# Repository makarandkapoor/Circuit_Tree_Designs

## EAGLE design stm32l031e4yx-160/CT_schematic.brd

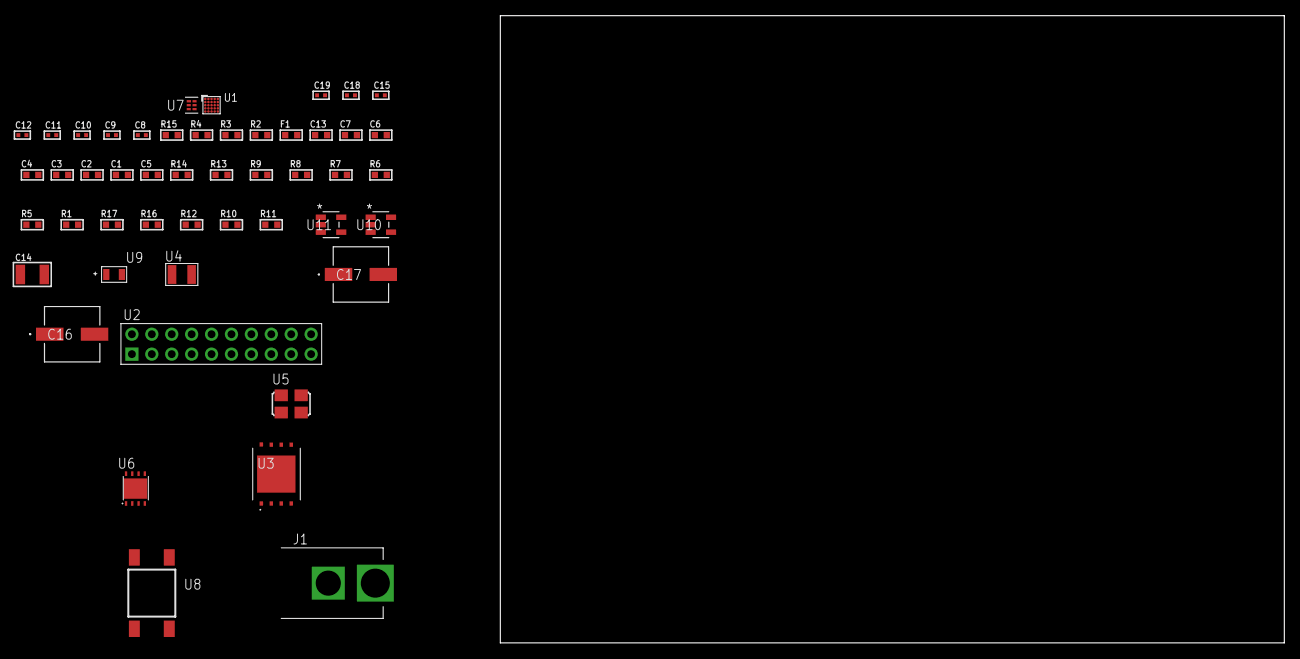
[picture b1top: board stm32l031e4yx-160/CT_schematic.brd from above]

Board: 2 copper layers, 100.0 x 80.0 mm, 49 parts (0 on the bottom side), 25 nets, no tracks yet.

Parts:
C1, C2, C3, C4: 1e-07; C0603
C5: 4.7e-06; C0603
C6: 1e-08; C0603
C7: 1e-06; C0603
C8, C9: 1e-11; C0402
C10, C15: 1e-07; C0402
C11, C12, C18, C19: 1e-08; C0402
C13: 8e-07; R0603
C14: 1e-05; C1210
C16, C17: 0.0001; EXV-9H
F1: 240.0; L0603
J1: PJ-037B; PJ-037B_PACKAGE
R1, R5, R6, R7, R8, R9, R13, R14: 10000.0; R0603
R2: 1000.0; R0603
R3: 1600.5; R0603
R4: 4700.0; R0603
R10, R12: 100000.0; R0603
R11: 153694.38; R0603
R15: 9100.0; R0603
R16: 680000.0; R0603
R17: 120000.0; R0603
U1: STM32L031E4Y6; WLCSP25
U2: TST-110-05-T-D-RA
U3: S25FL128SDPNFI001; WNG008
U4: ABS07-32.768KHZ-7-T
U5: ASFL1-12MHZ-NCS; ASFL1
U6: LP2951ACSDX/NOPB; WSON-8
U7: TPS3895ADRYR; SON-6
U8: 4-1437565-2; SW_4-1437565-2
U9: Q65110A2395; LGM67K-G1J2-24-Z
U10, U11: nc7sz125m5x; NC7SZ125M5X

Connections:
CLK_CRYSTAL_U1_B5: C8.1, U1.B5, U4.1
CLK_CRYSTAL_U1_C5: C9.1, U1.C5, U4.2
GND: C1.2, C2.2, C3.2, C4.2, C5.2, C6.2, C7.2, C8.2, C9.2, C10.2, C11.2, C12.2, C13.2, C14.2, C15.2, C16.2, C17.2, C18.2, C19.2, J1.2, R2.2, R5.2, R12.2, R15.2, R17.2, U1.E1, U2.4, U2.6, U2.8, U2.10, U2.12, U2.14, U2.16, U2.18, U2.20, U3.4, U3.PAD, U5.2, U6.3, U6.4, U6.PAD, U7.2, U9.C, U10.2, U10.3, U11.1, U11.3
NET_U1_A5: R5.1, U1.A5
NET_U1_C4: C6.1, C7.1, F1.1, U1.C4
NET_U1_D5: R4.1, U1.D5, U11.4
NET_U1_E4: R3.1, U1.E4, U9.A
NET_U1_E5: R1.1, U1.E5, U5.3, U8.3, U8.4
NET_U3_3: R7.1, U3.3
NET_U3_7: R9.1, U3.7
NET_U6_5: R10.1, U6.5
NET_U6_7: R11.2, R12.1, U6.7
NET_U7_1: R14.1, R15.1, U7.1
NET_U7_3: R16.2, R17.1, U7.3
NET_U7_4: R13.1, U7.4, U10.4, U11.2
NET_U8_1: R2.1, U8.1, U8.2
PROC_SPI1_MISO: U1.E2, U3.2
PROC_SPI1_MOSI: U1.C3, U3.5
PROC_SPI1_NSS: R8.1, U1.B3, U3.1
PROC_SPI1_SCK: U1.B2, U3.6
PROC_SYS_SWCLK: U1.A2, U2.9
PROC_SYS_SWDIO: U1.A1, U2.7
RST_OUT_U2_SRESET_B: R6.1, U2.15, U10.1
VCC_S1_12V7: C13.1, C16.1, C17.1, J1.1, U6.8
VCC_TIER1_3V3: C1.1, C2.1, C3.1, C4.1, C5.1, C10.1, C11.1, C12.1, C14.1, C15.1, C18.1, C19.1, F1.2, R1.2, R3.2, R4.2, R6.2, R7.2, R8.2, R9.2, R10.2, R11.1, R13.2, R14.2, R16.1, U1.D1, U2.1, U3.8, U5.4, U6.1, U7.6, U10.5, U11.5

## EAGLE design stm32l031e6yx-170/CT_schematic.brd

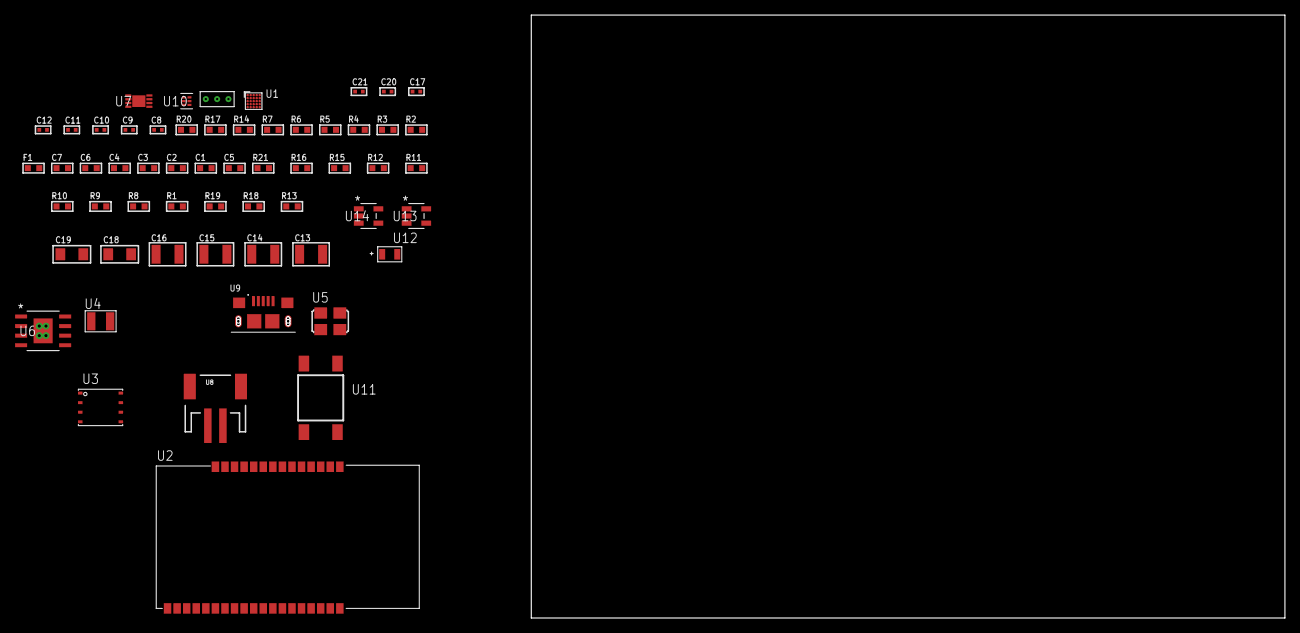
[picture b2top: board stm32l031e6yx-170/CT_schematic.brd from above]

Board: 2 copper layers, 58 parts (0 on the bottom side), 31 nets, no tracks yet.

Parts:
C1, C2, C3, C4: 1e-07; C0603
C5: 4.7e-06; C0603
C6: 1e-08; C0603
C7: 1e-06; C0603
C8, C9: 1e-11; C0402
C10, C17: 1e-07; C0402
C11, C12, C20, C21: 1e-08; C0402
C13, C14, C15, C16: 1e-05; C1210
C18, C19: 1e-05; C1206
F1: 240.0; L0603
R1, R8, R9, R10, R11, R12, R15, R16, R21: 10000.0; R0603
R2: 1000.0; R0603
R3: 1600.5; R0603
R4, R5: 4700.0; R0603
R6, R7, R14: 2200.0; R0603
R13: 4031.5447154472; R0603
R17: 9100.0; R0603
R18: 680000.0; R0603
R19: 120000.0; R0603
R20: 2000.0; R0603
U1: STM32L031E6Y6; WLCSP25
U2: ETRX3587
U3: 24AA512-I/MF; DFN8-S
U4: ABS07-32.768KHZ-7-T
U5: ASFL1-12MHZ-NCS; ASFL1
U6: MIC5234YME; SOIC-8_EP
U7: MCP73831T-2ACI/MC; DFN8_2X3MC
U8: S2B-PH-SM4-TB(LF)(SN); JST-2-SMD
U9: 10118193-0001LF; FCI_10118193-0001LF
U10: TPS3895ADRYR; SON-6
U11: 4-1437565-2; SW_4-1437565-2
U12: Q65110A2395; LGM67K-G1J2-24-Z
U13, U14: nc7sz125m5x; NC7SZ125M5X
U15: Dummy; DUMMY_PACKAGE_122

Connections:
CLK_CRYSTAL_U1_B5: C8.1, U1.B5, U4.1
CLK_CRYSTAL_U1_C5: C9.1, U1.C5, U4.2
GND: C1.2, C2.2, C3.2, C4.2, C5.2, C6.2, C7.2, C8.2, C9.2, C10.2, C11.2, C12.2, C13.2, C14.2, C15.2, C16.2, C17.2, C18.2, C19.2, C20.2, C21.2, R2.2, R8.2, R9.2, R12.2, R14.2, R17.2, R19.2, R20.2, U1.E1, U2.1, U2.13, U2.19, U2.20, U2.31, U2.33, U3.4, U3.7, U5.2, U6.7, U6.EPAD, U7.6, U7.9, U8.2, U9.5, U9.6, U9.7, U9.8, U9.9, U10.2, U12.C, U13.1, U13.3, U14.1, U14.3, U15.1
INPUT_USBPOWER_5V: C18.1, R21.2, U7.1, U7.2, U9.1
NET_U1_A3: R6.1, U1.A3, U3.6
NET_U1_A4: R7.1, U1.A4, U3.5
NET_U1_A5: R8.1, U1.A5
NET_U1_C4: C6.1, C7.1, F1.1, U1.C4
NET_U1_D5: R5.1, U1.D5, U14.4
NET_U1_E4: R3.1, U1.E4, U12.A
NET_U1_E5: R1.1, U1.E5, U5.3, U11.3, U11.4
NET_U2_7: R4.1, U2.7, U13.4
NET_U2_21: R9.1, U2.21
NET_U3_1: R10.1, U3.1
NET_U3_2: R11.1, U3.2
NET_U3_3: R12.1, U3.3
NET_U6_4: R13.2, R14.1, U6.4
NET_U7_5: R21.1, U7.5
NET_U7_8: R20.1, U7.8
NET_U10_1: R16.1, R17.1, U10.1
NET_U10_3: R18.2, R19.1, U10.3
NET_U10_4: R15.1, U10.4, U13.2, U14.2
NET_U11_1: R2.1, U11.1, U11.2
PROC_LPUART1_CTS: U1.E3, U2.8
PROC_LPUART1_RTS: U1.D2, U2.6
PROC_LPUART1_RX: U1.A1, U2.17
PROC_LPUART1_TX: U1.A2, U2.18
PROC_TIM2_CH2: U1.B2, U15.3
PROC_TIM2_CH3: U1.D4, U15.2
VCC_S1_3V7: C13.1, C14.1, C19.1, U6.5, U6.8, U7.3, U7.4, U8.1
VCC_TIER1_3V3: C1.1, C2.1, C3.1, C4.1, C5.1, C10.1, C11.1, C12.1, C15.1, C16.1, C17.1, C20.1, C21.1, F1.2, R1.2, R3.2, R4.2, R5.2, R6.2, R7.2, R10.2, R11.2, R13.1, R15.2, R16.2, R18.1, U1.D1, U2.32, U3.8, U5.4, U6.1, U10.6, U13.5, U14.5

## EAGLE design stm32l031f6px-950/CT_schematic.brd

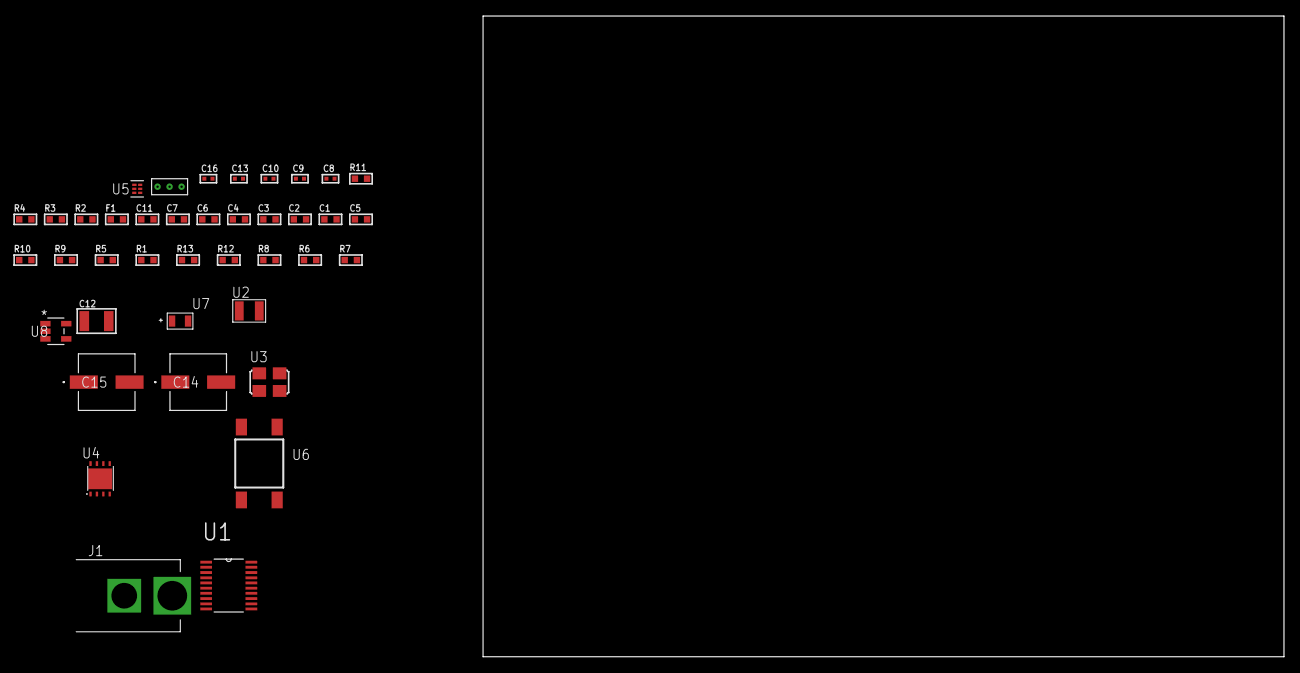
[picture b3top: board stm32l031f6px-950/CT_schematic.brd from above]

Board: 2 copper layers, 100.0 x 80.0 mm, 40 parts (0 on the bottom side), 19 nets, no tracks yet.

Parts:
C1, C2, C3, C4: 1e-07; C0603
C5: 4.7e-06; C0603
C6: 1e-08; C0603
C7, C11: 1e-06; C0603
C8, C9: 1e-11; C0402
C10, C16: 1e-08; C0402
C12: 1e-05; C1210
C13: 1e-07; C0402
C14, C15: 0.0001; EXV-9H
F1: 240.0; L0603
J1: PJ-037B; PJ-037B_PACKAGE
R1, R5, R9, R10: 10000.0; R0603
R2: 1000.0; R0603
R3: 1600.5; R0603
R4: 4700.0; R0603
R6, R8: 100000.0; R0603
R7: 153694.38; R0603
R11: 9100.0; R0603
R12: 680000.0; R0603
R13: 120000.0; R0603
U1: STM32L031F6P6; TSSOP20
U2: ABS07-32.768KHZ-7-T
U3: ASFL1-12MHZ-NCS; ASFL1
U4: LP2951ACSDX/NOPB; WSON-8
U5: TPS3895ADRYR; SON-6
U6: 4-1437565-2; SW_4-1437565-2
U7: Q65110A2395; LGM67K-G1J2-24-Z
U8: nc7sz125m5x; NC7SZ125M5X
U9: Dummy; DUMMY_PACKAGE_78

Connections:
CLK_CRYSTAL_U1_2: C8.1, U1.2, U2.1
CLK_CRYSTAL_U1_3: C9.1, U1.3, U2.2
CLK_U1_6: U1.6, U3.3
GND: C1.2, C2.2, C3.2, C4.2, C5.2, C6.2, C7.2, C8.2, C9.2, C10.2, C11.2, C12.2, C13.2, C14.2, C15.2, C16.2, J1.2, R2.2, R5.2, R8.2, R11.2, R13.2, U1.15, U3.2, U4.3, U4.4, U4.PAD, U5.2, U7.C, U8.1, U8.3, U9.1
NET_U1_1: R5.1, U1.1
NET_U1_4: R4.1, U1.4, U8.4
NET_U1_5: C6.1, C7.1, F1.1, U1.5
NET_U1_19: R3.1, U1.19, U7.A
NET_U1_20: R1.1, U1.20, U6.3, U6.4
NET_U4_5: R6.1, U4.5
NET_U4_7: R7.2, R8.1, U4.7
NET_U5_1: R10.1, R11.1, U5.1
NET_U5_3: R12.2, R13.1, U5.3
NET_U5_4: R9.1, U5.4, U8.2
NET_U6_1: R2.1, U6.1, U6.2
PROC_ADC_IN4: U1.10, U9.2
PROC_ADC_IN6: U1.12, U9.3
VCC_S1_10V3: C11.1, C14.1, C15.1, J1.1, U4.8
VCC_TIER1_3V3: C1.1, C2.1, C3.1, C4.1, C5.1, C10.1, C12.1, C13.1, C16.1, F1.2, R1.2, R3.2, R4.2, R6.2, R7.1, R9.2, R10.2, R12.1, U1.16, U3.4, U4.1, U5.6, U8.5

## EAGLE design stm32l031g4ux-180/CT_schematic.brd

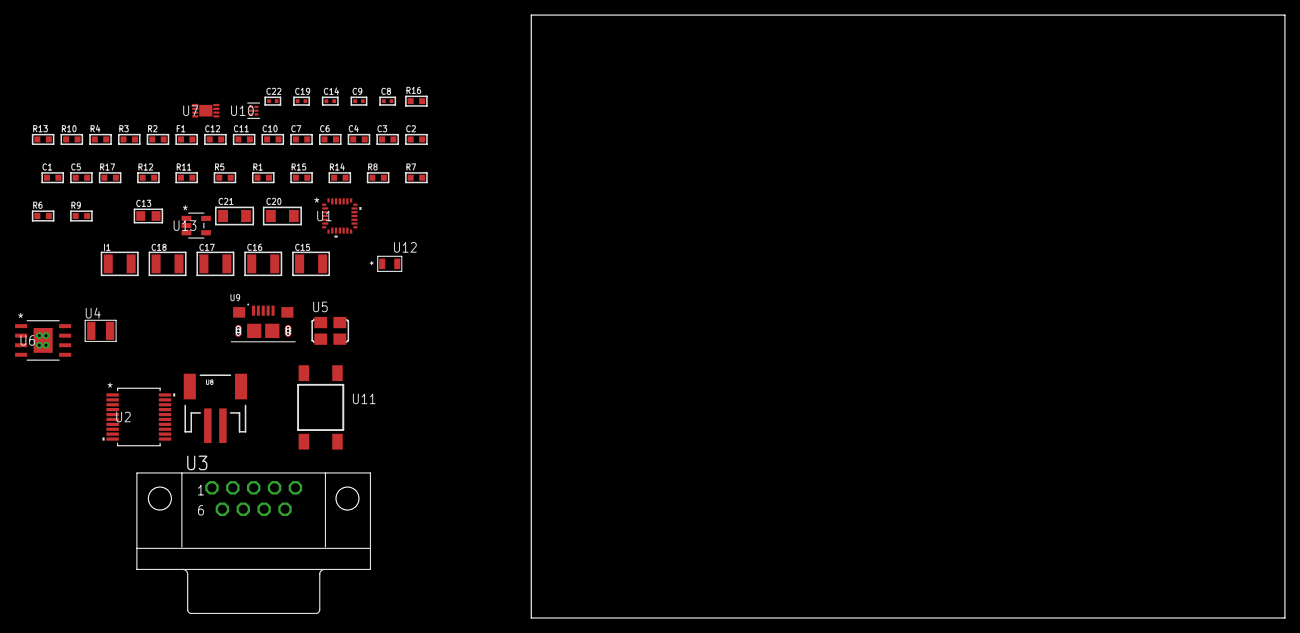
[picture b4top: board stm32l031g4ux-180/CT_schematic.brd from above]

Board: 2 copper layers, 54 parts (0 on the bottom side), 35 nets, no tracks yet.

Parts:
C1, C2, C3, C4: 1e-07; C0603
C5: 4.7e-06; C0603
C6: 1e-08; C0603
C7, C10, C11, C12: 1e-06; C0603
C8, C9: 1e-11; C0402
C13: 4.7e-06; C0805
C14, C22: 1e-08; C0402
C15, C16, C17, C18: 1e-05; C1210
C19: 1e-07; C0402
C20, C21: 1e-05; C1206
F1: 240.0; L0603
I1: 1.5e-05; L1210
R1, R5, R11, R12, R17: 10000.0; R0603
R2: 1000.0; R0603
R3: 1600.5; R0603
R4: 4700.0; R0603
R6, R7, R8: 100000.0; R0603
R9: 4031.5447154472; R0603
R10: 2200.0; R0603
R13: 9100.0; R0603
R14: 680000.0; R0603
R15: 120000.0; R0603
R16: 2000.0; R0603
U1: STM32L031G4U6; UFQFPN28
U2: MAX3218EAP+T; SSOP-20
U3: 182-009-113R531; 182-009-MALE
U4: ABS07-32.768KHZ-7-T
U5: ASFL1-12MHZ-NCS; ASFL1
U6: MIC5234YME; SOIC-8_EP
U7: MCP73831T-2ACI/MC; DFN8_2X3MC
U8: S2B-PH-SM4-TB(LF)(SN); JST-2-SMD
U9: 10118193-0001LF; FCI_10118193-0001LF
U10: TPS3895ADRYR; SON-6
U11: 4-1437565-2; SW_4-1437565-2
U12: Q65110A2395; LGM67K-G1J2-24-Z
U13: nc7sz125m5x; NC7SZ125M5X

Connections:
CLK_CRYSTAL_U1_2: C8.1, U1.2, U4.1
CLK_CRYSTAL_U1_3: C9.1, U1.3, U4.2
CLK_U1_6: U1.6, U5.3
GND: C1.2, C2.2, C3.2, C4.2, C5.2, C6.2, C7.2, C8.2, C9.2, C10.2, C11.2, C12.2, C14.2, C15.2, C16.2, C17.2, C18.2, C19.2, C20.2, C21.2, C22.2, R2.2, R5.2, R10.2, R13.2, R15.2, R16.2, U1.16, U1.28, U2.5, U2.17, U2.20, U3.5, U5.2, U6.7, U6.EPAD, U7.6, U7.9, U8.2, U9.5, U9.6, U9.7, U9.8, U9.9, U10.2, U12.C, U13.1, U13.3
INPUT_USBPOWER_5V: C20.1, R17.2, U7.1, U7.2, U9.1
NET_U1_4: R4.1, U1.4, U13.4
NET_U1_5: C6.1, C7.1, F1.1, U1.5
NET_U1_25: R3.1, U1.25, U12.A
NET_U1_26: R1.1, U1.26, U11.3, U11.4
NET_U1_27: R5.1, U1.27
NET_U2_1: I1.1, U2.1
NET_U2_2: R6.1, U2.2
NET_U2_3: R7.1, U2.3
NET_U2_4: R8.1, U2.4
NET_U2_15: C12.1, U2.15
NET_U2_16: C13.2, U2.16
NET_U2_18: C13.1, U2.18
NET_U2_19: C11.1, U2.19
NET_U3_2: U2.12, U3.2
NET_U3_3: U2.14, U3.3
NET_U3_7: U2.11, U3.7
NET_U3_8: U2.13, U3.8
NET_U6_4: R9.2, R10.1, U6.4
NET_U7_5: R17.1, U7.5
NET_U7_8: R16.1, U7.8
NET_U10_1: R12.1, R13.1, U10.1
NET_U10_3: R14.2, R15.1, U10.3
NET_U10_4: R11.1, U10.4, U13.2
NET_U11_1: R2.1, U11.1, U11.2
PROC_LPUART1_CTS: U1.12, U2.8
PROC_LPUART1_RTS: U1.15, U2.10
PROC_LPUART1_RX: U1.9, U2.9
PROC_LPUART1_TX: U1.8, U2.7
VCC_S1_3V7: C15.1, C16.1, C21.1, U6.5, U6.8, U7.3, U7.4, U8.1
VCC_TIER1_3V3: C1.1, C2.1, C3.1, C4.1, C5.1, C10.1, C14.1, C17.1, C18.1, C19.1, C22.1, F1.2, I1.2, R1.2, R3.2, R4.2, R6.2, R7.2, R8.2, R9.1, R11.2, R12.2, R14.1, U1.1, U1.17, U2.6, U5.4, U6.1, U10.6, U13.5

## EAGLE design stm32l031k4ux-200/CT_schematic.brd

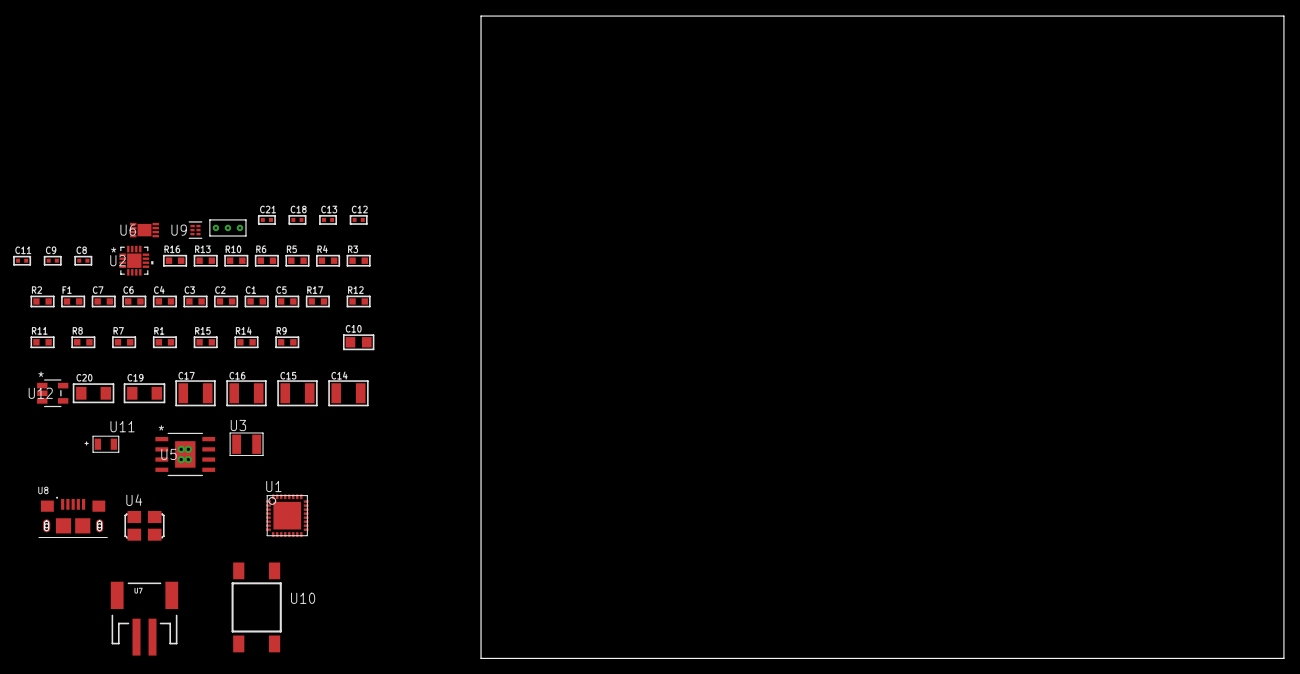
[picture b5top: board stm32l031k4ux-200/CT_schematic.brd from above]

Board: 2 copper layers, 154.3 x 80.0 mm, 52 parts (0 on the bottom side), 25 nets, no tracks yet.

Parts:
C1, C2, C3, C4: 1e-07; C0603
C5: 4.7e-06; C0603
C6: 1e-08; C0603
C7: 1e-06; C0603
C8, C9: 1e-11; C0402
C10: 4.7e-06; C0805
C11, C12, C18: 1e-07; C0402
C13, C21: 1e-08; C0402
C14, C15, C16, C17: 1e-05; C1210
C19, C20: 1e-05; C1206
F1: 240.0; L0603
R1, R7, R8, R11, R12, R17: 10000.0; R0603
R2: 1000.0; R0603
R3: 1600.5; R0603
R4: 4700.0; R0603
R5, R6, R10: 2200.0; R0603
R9: 4031.5447154472; R0603
R13: 9100.0; R0603
R14: 680000.0; R0603
R15: 120000.0; R0603
R16: 2000.0; R0603
U1: STM32L031K4U6; UFQFPN32
U2: MMA8451QT; QFN-16
U3: ABS07-32.768KHZ-7-T
U4: ASFL1-12MHZ-NCS; ASFL1
U5: MIC5234YME; SOIC-8_EP
U6: MCP73831T-2ACI/MC; DFN8_2X3MC
U7: S2B-PH-SM4-TB(LF)(SN); JST-2-SMD
U8: 10118193-0001LF; FCI_10118193-0001LF
U9: TPS3895ADRYR; SON-6
U10: 4-1437565-2; SW_4-1437565-2
U11: Q65110A2395; LGM67K-G1J2-24-Z
U12: nc7sz125m5x; NC7SZ125M5X
U13: Dummy; DUMMY_PACKAGE_107

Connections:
CLK_CRYSTAL_U1_2: C8.1, U1.2, U3.1
CLK_CRYSTAL_U1_3: C9.1, U1.3, U3.2
CLK_U1_6: U1.6, U4.3
GND: C1.2, C2.2, C3.2, C4.2, C5.2, C6.2, C7.2, C8.2, C9.2, C10.2, C11.2, C12.2, C13.2, C14.2, C15.2, C16.2, C17.2, C18.2, C19.2, C20.2, C21.2, R2.2, R7.2, R8.2, R10.2, R13.2, R15.2, R16.2, U1.EPAD, U2.5, U2.10, U2.12, U2.17, U4.2, U5.7, U5.EPAD, U6.6, U6.9, U7.2, U8.5, U8.6, U8.7, U8.8, U8.9, U9.2, U11.C, U12.1, U12.3, U13.1
INPUT_USBPOWER_5V: C19.1, R17.2, U6.1, U6.2, U8.1
NET_U1_4: R4.1, U1.4, U12.4
NET_U1_5: C6.1, C7.1, F1.1, U1.5
NET_U1_19: R5.1, U1.19, U2.4
NET_U1_20: R6.1, U1.20, U2.6
NET_U1_30: R3.1, U1.30, U11.A
NET_U1_31: R7.1, U1.31
NET_U1_32: R1.1, U1.32, U10.3, U10.4
NET_U2_2: C12.1, U2.2
NET_U2_7: R8.1, U2.7
NET_U5_4: R9.2, R10.1, U5.4
NET_U6_5: R17.1, U6.5
NET_U6_8: R16.1, U6.8
NET_U9_1: R12.1, R13.1, U9.1
NET_U9_3: R14.2, R15.1, U9.3
NET_U9_4: R11.1, U9.4, U12.2
NET_U10_1: R2.1, U10.1, U10.2
PROC_TIM2_CH3: U1.8, U13.3
PROC_TIM2_CH4: U1.9, U13.2
VCC_S1_3V7: C14.1, C15.1, C20.1, U5.5, U5.8, U6.3, U6.4, U7.1
VCC_TIER1_3V3: C1.1, C2.1, C3.1, C4.1, C5.1, C10.1, C11.1, C13.1, C16.1, C17.1, C18.1, C21.1, F1.2, R1.2, R3.2, R4.2, R5.2, R6.2, R9.1, R11.2, R12.2, R14.1, U1.1, U1.17, U2.1, U2.14, U4.4, U5.1, U9.6, U12.5

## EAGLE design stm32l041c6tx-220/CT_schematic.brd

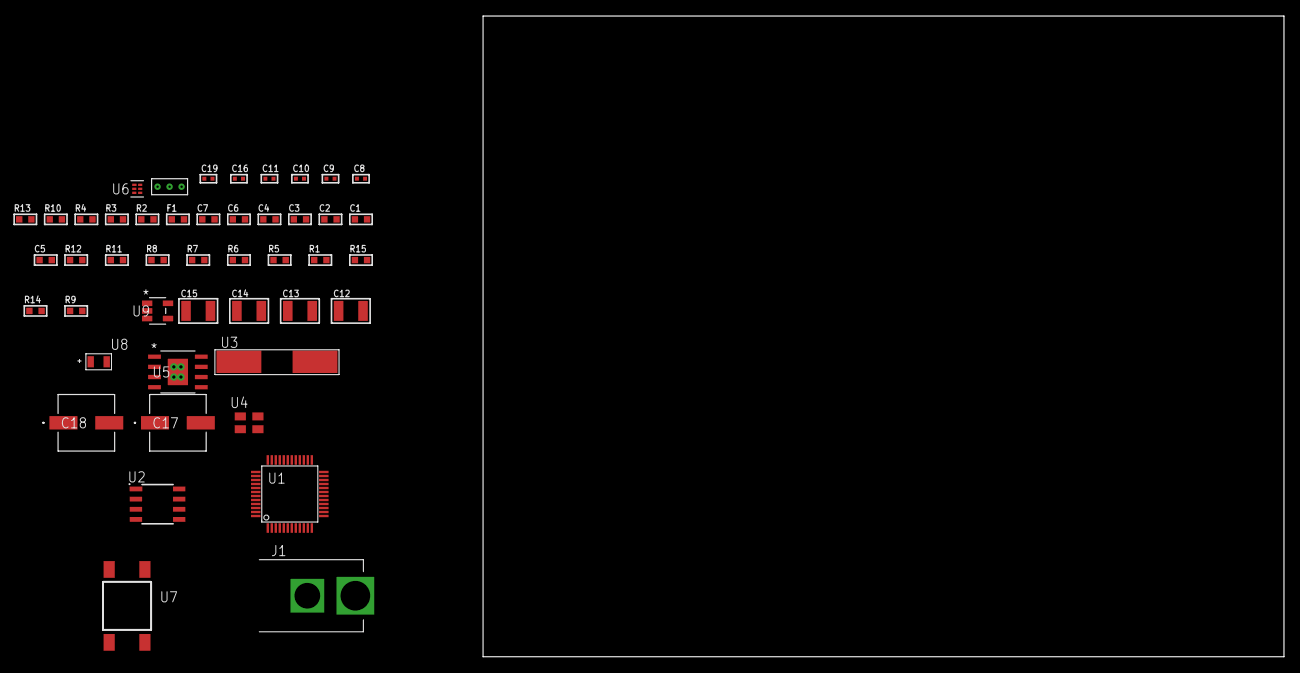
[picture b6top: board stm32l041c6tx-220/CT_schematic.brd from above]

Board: 2 copper layers, 100.0 x 80.0 mm, 46 parts (0 on the bottom side), 24 nets, no tracks yet.

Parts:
C1, C2, C3, C4: 1e-07; C0603
C5: 4.7e-06; C0603
C6: 1e-08; C0603
C7: 1e-06; C0603
C8, C9: 1e-11; C0402
C10, C11, C19: 1e-08; C0402
C12, C13, C14, C15: 1e-05; C1210
C16: 1e-07; C0402
C17, C18: 0.0001; EXV-9H
F1: 240.0; L0603
J1: PJ-037B; PJ-037B_PACKAGE
R1, R5, R6, R7, R8, R11, R12: 10000.0; R0603
R2: 1000.0; R0603
R3: 1600.5; R0603
R4: 4700.0; R0603
R9: 4031.5447154472; R0603
R10: 2200.0; R0603
R13: 9100.0; R0603
R14: 680000.0; R0603
R15: 120000.0; R0603
U1: STM32L041C6T6; LQFP48
U2: AT25M01-SSHM-T; SOIC-8
U3: ABLS-25.000MHZ-B2F-T
U4: ASEK-32.768KHz-ECST; ASEK
U5: MIC5234YME; SOIC-8_EP
U6: TPS3895ADRYR; SON-6
U7: 4-1437565-2; SW_4-1437565-2
U8: Q65110A2395; LGM67K-G1J2-24-Z
U9: nc7sz125m5x; NC7SZ125M5X
U10: Dummy; DUMMY_PACKAGE_90

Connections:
CLK_CRYSTAL_U1_5: C8.1, U1.5, U3.1
CLK_CRYSTAL_U1_6: C9.1, U1.6, U3.2
CLK_U1_3: U1.3, U4.3
GND: C1.2, C2.2, C3.2, C4.2, C5.2, C6.2, C7.2, C8.2, C9.2, C10.2, C11.2, C12.2, C13.2, C14.2, C15.2, C16.2, C17.2, C18.2, C19.2, J1.2, R2.2, R5.2, R10.2, R13.2, R15.2, U1.8, U1.23, U1.35, U1.47, U2.4, U4.2, U5.7, U5.EPAD, U6.2, U8.C, U9.1, U9.3, U10.1
NET_U1_7: R4.1, U1.7, U9.4
NET_U1_9: C6.1, C7.1, F1.1, U1.9
NET_U1_44: R5.1, U1.44
NET_U1_45: R3.1, U1.45, U8.A
NET_U1_46: R1.1, U1.46, U7.3, U7.4
NET_U2_3: R6.1, U2.3
NET_U2_7: R8.1, U2.7
NET_U5_4: R9.2, R10.1, U5.4
NET_U6_1: R12.1, R13.1, U6.1
NET_U6_3: R14.2, R15.1, U6.3
NET_U6_4: R11.1, U6.4, U9.2
NET_U7_1: R2.1, U7.1, U7.2
PROC_ADC_IN1: U1.11, U10.3
PROC_ADC_IN9: U1.19, U10.2
PROC_SPI1_MISO: U1.16, U2.2
PROC_SPI1_MOSI: U1.17, U2.5
PROC_SPI1_NSS: R7.1, U1.14, U2.1
PROC_SPI1_SCK: U1.15, U2.6
VCC_S1_14V3: C12.1, C13.1, C17.1, C18.1, J1.1, U5.5, U5.8
VCC_TIER1_3V3: C1.1, C2.1, C3.1, C4.1, C5.1, C10.1, C11.1, C14.1, C15.1, C16.1, C19.1, F1.2, R1.2, R3.2, R4.2, R6.2, R7.2, R8.2, R9.1, R11.2, R12.2, R14.1, U1.24, U1.36, U1.48, U2.8, U4.4, U5.1, U6.6, U9.5

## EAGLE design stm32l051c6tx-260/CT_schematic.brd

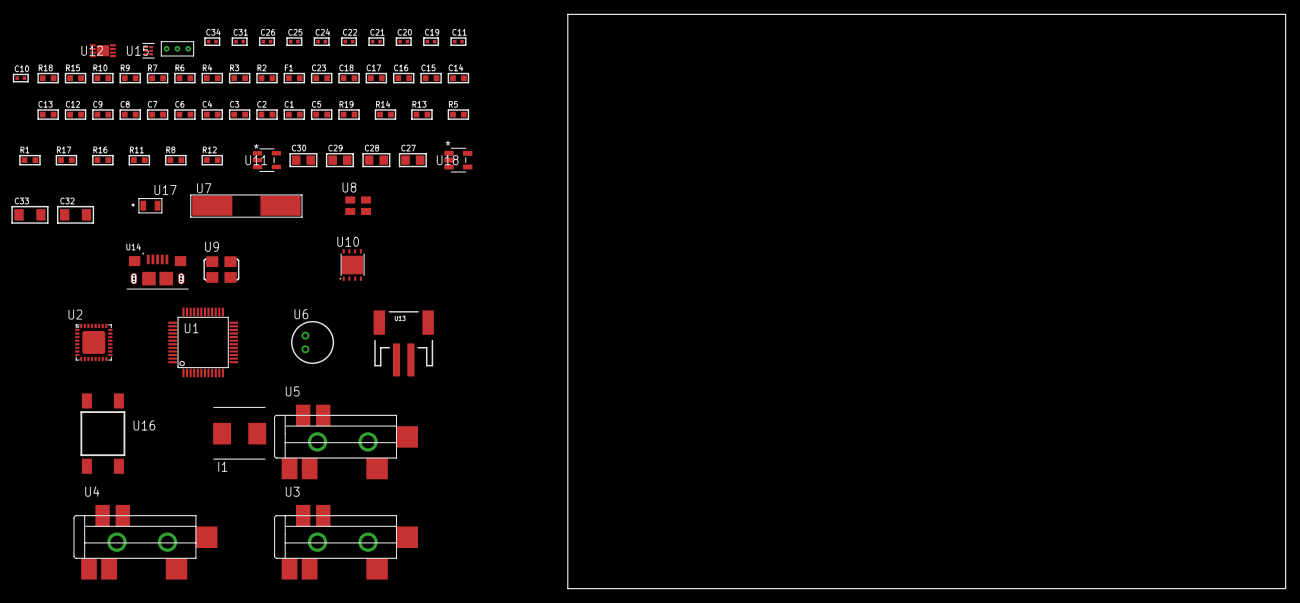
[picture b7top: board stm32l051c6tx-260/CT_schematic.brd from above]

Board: 2 copper layers, 74 parts (0 on the bottom side), 44 nets, no tracks yet.

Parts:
C1, C2, C3, C4, C6, C7: 1e-07; C0603
C5: 4.7e-06; C0603
C8: 1e-08; C0603
C9, C12, C13, C14, C15, C16, C17, C18, C23: 1e-06; C0603
C10, C11: 1e-11; C0402
C19, C20, C21, C22, C31: 1e-07; C0402
C24, C25, C26, C34: 1e-08; C0402
C27, C28, C29, C30: 1e-05; C0805
C32, C33: 1e-05; C1206
F1: 240.0; L0603
I1: 2e-06; WE-HCI_7030/7040/7050
R1, R5, R13, R14, R19: 10000.0; R0603
R2, R10: 1000.0; R0603
R3: 1600.5; R0603
R4: 4700.0; R0603
R6, R7: 1270.0; R0603
R8: 100000.0; R0603
R9: 200.0; R0603
R11: 220000.0; R0603
R12: 1000000.0; R0603
R15: 9100.0; R0603
R16: 680000.0; R0603
R17: 120000.0; R0603
R18: 2000.0; R0603
U1: STM32L051C6T6; LQFP48
U2: SGTL5000XNAA3; QFN-32
U3, U4, U5: SJ-43515TS-SMT-TR
U6: WM-64PCT; WM-64PC
U7: ABLS-25.000MHZ-B2F-T
U8: ASEK-32.768KHz-ECST; ASEK
U9: ASFL-24.57MHZ-NCS; ASFL1
U10: LP3878SDX-ADJ/NOPB; WSON-8
U11: ltc3406es5; TSOT-23-5
U12: MCP73831T-2ACI/MC; DFN8_2X3MC
U13: S2B-PH-SM4-TB(LF)(SN); JST-2-SMD
U14: 10118193-0001LF; FCI_10118193-0001LF
U15: TPS3895ADRYR; SON-6
U16: 4-1437565-2; SW_4-1437565-2
U17: Q65110A2395; LGM67K-G1J2-24-Z
U18: nc7sz125m5x; NC7SZ125M5X
U19: Dummy; DUMMY_PACKAGE_147

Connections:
CLK_CRYSTAL_U1_5: C10.1, U1.5, U7.1
CLK_CRYSTAL_U1_6: C11.1, U1.6, U7.2
CLK_U1_3: U1.3, U8.3
CLK_U2_21: U2.21, U9.3
GND: C1.2, C2.2, C3.2, C4.2, C5.2, C6.2, C7.2, C8.2, C9.2, C10.2, C11.2, C19.2, C20.2, C21.2, C22.2, C23.2, C24.2, C25.2, C26.2, C27.2, C28.2, C29.2, C30.1, C30.2, C31.2, C32.2, C33.2, C34.2, R2.2, R5.2, R7.2, R10.2, R11.2, R15.2, R17.2, R18.2, U1.8, U1.23, U1.35, U1.47, U2.1, U2.3, U2.7, U2.EXP, U4.1, U5.1, U6.2, U8.2, U9.2, U10.3, U10.PAD, U11.2, U12.6, U12.9, U13.2, U14.5, U14.6, U14.7, U14.8, U14.9, U15.2, U17.C, U18.1, U18.3, U19.1
INPUT_USBPOWER_5V: C32.1, R19.2, U12.1, U12.2, U14.1
NET_U1_7: R4.1, U1.7, U18.4
NET_U1_9: C8.1, C9.1, F1.1, U1.9
NET_U1_44: R5.1, U1.44
NET_U1_45: R3.1, U1.45, U17.A
NET_U1_46: R1.1, U1.46, U16.3, U16.4
NET_U2_10: C22.1, U2.10
NET_U2_29: R6.1, U2.29
NET_U2_31: R7.1, U2.31
NET_U3_1: U2.4, U3.1
NET_U3_2: U2.2, U3.2
NET_U3_5: U2.6, U3.5
NET_U4_2: C13.1, U4.2
NET_U4_5: C12.1, U4.5
NET_U5_2: C15.1, C16.1, U5.2
NET_U5_5: C14.1, U5.5
NET_U5_13: C15.2, C16.2
NET_U6_1: C17.1, C18.1, C23.1, U2.16, U6.1
NET_U6_15: C17.2, C18.2
NET_U10_1: C26.1, U10.1
NET_U10_6: R9.2, R10.1, U10.6
NET_U10_8: R8.1, U10.8
NET_U11_3: I1.1, U11.3
NET_U11_5: R11.1, R12.1, U11.5
NET_U11_ATNET_3: I1.2, R12.2
NET_U12_5: R19.1, U12.5
NET_U12_8: R18.1, U12.8
NET_U15_1: R14.1, R15.1, U15.1
NET_U15_3: R16.2, R17.1, U15.3
NET_U15_4: R13.1, U15.4, U18.2
NET_U16_1: R2.1, U16.1, U16.2
PROC_I2S2_CK: U1.26, U2.24
PROC_I2S2_SD: U1.28, U2.26
PROC_I2S2_WS: U1.25, U2.23
PROC_TIM2_CH3: U1.12, U19.3
PROC_TIM2_CH4: U1.13, U19.2
VCC_S1_3V7: C27.1, C29.1, C33.1, R8.2, U10.4, U11.4, U12.3, U12.4, U13.1
VCC_TIER1_1V2: C19.1, C28.1, R9.1, U2.30, U10.5
VCC_TIER1_3V3: C1.1, C2.1, C3.1, C4.1, C5.1, C6.1, C7.1, C20.1, C21.1, C24.1, C25.1, C30.2, C31.1, C34.1, F1.2, I1.2, R1.2, R3.2, R4.2, R6.2, R12.2, R13.2, R14.2, R16.1, U1.1, U1.24, U1.36, U1.48, U2.5, U2.20, U8.4, U9.4, U15.6, U18.5
